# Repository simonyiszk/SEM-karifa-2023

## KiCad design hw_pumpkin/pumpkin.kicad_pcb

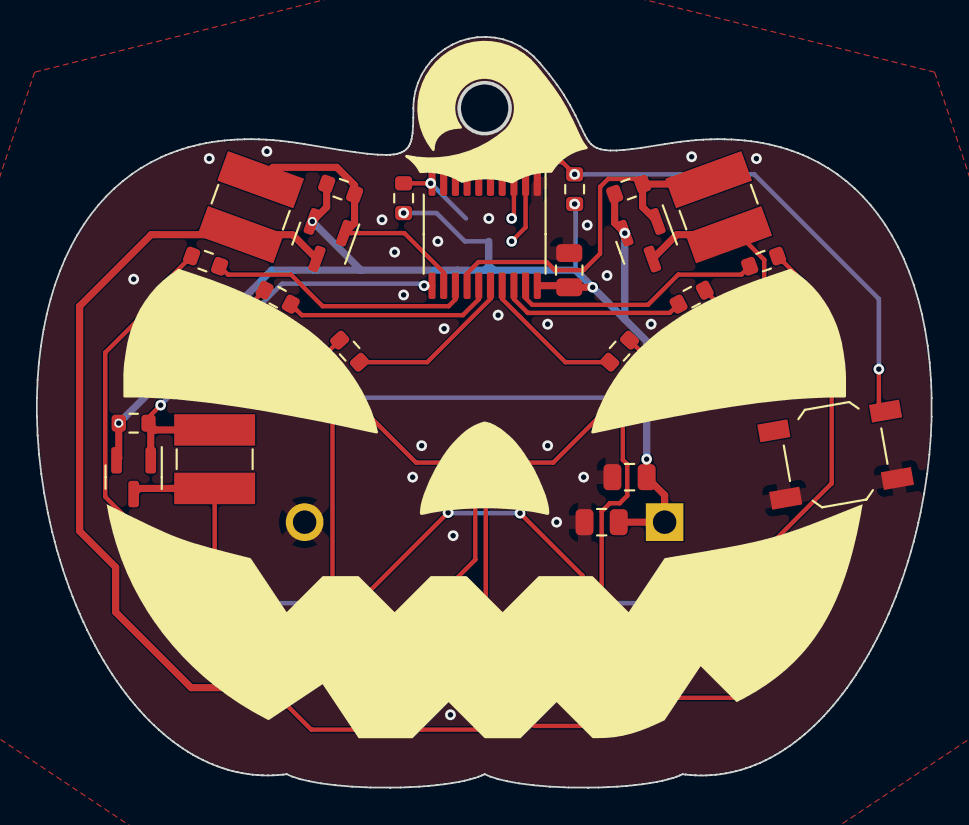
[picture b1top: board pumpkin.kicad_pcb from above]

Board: 2 copper layers, 49.7 x 41.7 mm, 44 parts (1 on the bottom side), 22 nets.

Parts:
BT1: CR2032; CR2032_Holder
C1, C2: 10uF; C_0805_2012Metric
C3: 100nF; C_0805_2012Metric
D1, D2, D3, D4, D5, D6, D7, D8, D9, D10, D11, D12, D13, D14, D15, D16, D17, D18: LED; LED_0805_2012Metric
L1, L2, L3: 1mH; L_Ferrocore_DLG-0403
Q1, Q2, Q3: AO3401A; SOT-23
R1, R6#2, R8, R9, R10: 100k; R_0603_1608Metric
R2, R3, R4, R5, R6, R7: 10; R_0603_1608Metric
SW1: SW_DPST_x2; SW_SPST_TL3342
T1, T1#2, T1#3: Tab
U1: PY32F002AF15P6TU; TSSOP-20_4.4x6.5mm_P0.65mm

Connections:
/L1: R2.2, U1.13 (PA2)
/L2: R3.2, U1.15 (PA4)
/L3: R4.2, U1.16 (PA7)
/L4: R5.2, U1.17 (PB0)
/L5: R6.2, U1.18 (PB2)
/L6: R7.2, U1.19 (PB1)
/MPX1: L1.2, Q1.1 (G), R1.2, U1.12 (PA1)
/MPX2: L2.2, Q2.1 (G), R8.2, U1.11 (PA0)
/MPX3: L3.2, Q3.1 (G), R10.2, U1.14 (PA3)
/nRST: R6#2.1, U1.10 (PF2-NRST)
GND: BT1.2 (-), C1.2, C2.2, C3.1, SW1.2 (B), U1.1 (VSS)
unnamed: D1.2 (A), D7.2 (A), D13.2 (A), R2.1
unnamed: D1.1 (K), D2.1 (K), D3.1 (K), D4.1 (K), D5.1 (K), D6.1 (K), L1.1, Q1.3 (D)
unnamed: D4.2 (A), D10.2 (A), D16.2 (A), R5.1
unnamed: D7.1 (K), D8.1 (K), D9.1 (K), D10.1 (K), D11.1 (K), D12.1 (K), L2.1, Q2.3 (D)
unnamed: D5.2 (A), D11.2 (A), D17.2 (A), R6.1
unnamed: D6.2 (A), D12.2 (A), D18.2 (A), R7.1
unnamed: D13.1 (K), D14.1 (K), D15.1 (K), D16.1 (K), D17.1 (K), D18.1 (K), L3.1, Q3.3 (D)
unnamed: D2.2 (A), D8.2 (A), D14.2 (A), R3.1
unnamed: D3.2 (A), D9.2 (A), D15.2 (A), R4.1
unnamed: R9.1, SW1.1 (A), U1.4 (PB3)
VCC: BT1.1 (+), C1.1, C2.1, C3.2, Q1.2 (S), Q2.2 (S), Q3.2 (S), R1.1, R6#2.2, R8.1, R9.2, R10.1, U1.20 (VCC)

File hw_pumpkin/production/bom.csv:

Designator,Footprint,Quantity,Value,LCSC Part #
BT1,CR2032_Holder,1,CR2032,
"C1, C2",0805,2,10uF,
C3,0805,1,100nF,
"D1, D10, D11, D12, D13, D14, D15, D16, D17, D18, D2, D3, D4, D5, D6, D7, D8, D9",0805,18,LED,
"L1, L2, L3",L_Ferrocore_DLG-0403,3,1mH,
"Q1, Q2, Q3",SOT-23,3,AO3401A,
"R1, R10, R6, R8, R9",0603,5,100k,
"R2, R3, R4, R5, R6_2, R7",0603,6,10,
SW1,SW_SPST_TL3342,1,SW_DPST_x2,
U1,TSSOP-20_4.4x6.5mm_P0.65mm,1,PY32F002AF15P6TU,

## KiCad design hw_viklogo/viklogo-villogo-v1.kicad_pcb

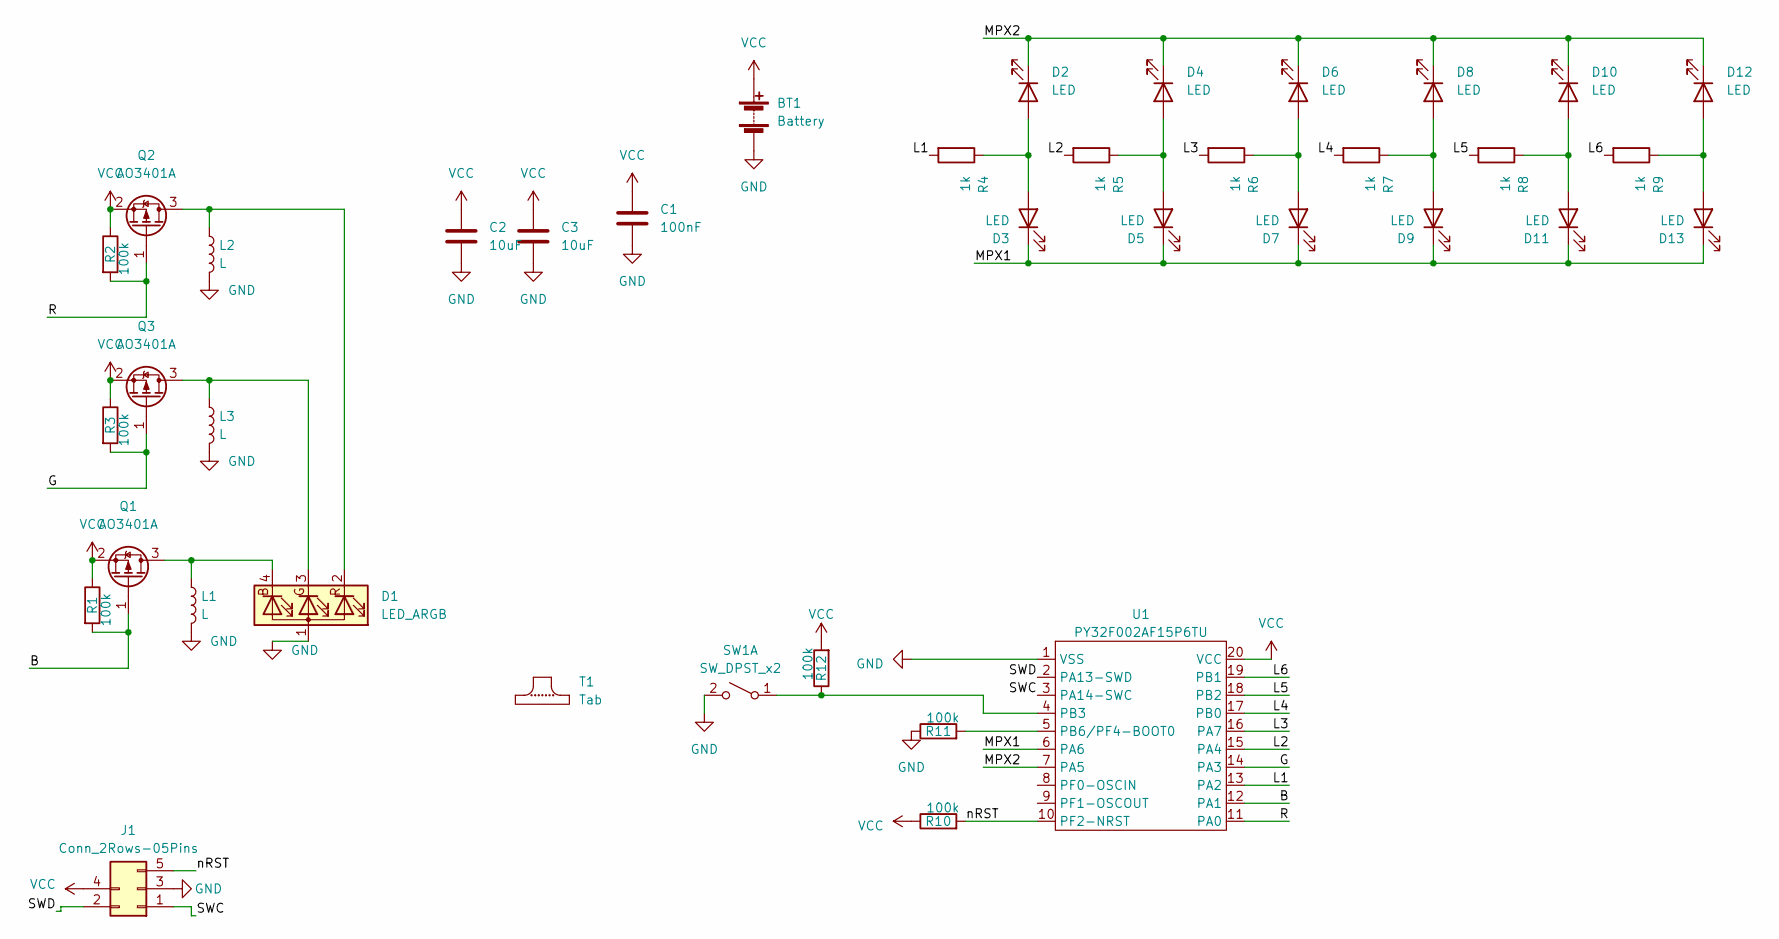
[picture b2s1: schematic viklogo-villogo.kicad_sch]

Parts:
BT1: Battery; CR2032_Holder
C1: 100nF; C_0805_2012Metric
C2, C3: 10uF; C_0805_2012Metric
D1: LED_ARGB; LED_RGB_Wuerth-PLCC4_3.2x2.8mm_150141M173100
D2, D3, D4, D5, D6, D7, D8, D9, D10, D11, D12, D13: LED; LED_0805_2012Metric
J1: Conn_2Rows-05Pins; ProgConnector_5pin
L1, L2, L3: L; L_1008_2520Metric
Q1, Q2, Q3: AO3401A; SOT-23
R1, R2, R3, R10, R11, R12: 100k; R_0603_1608Metric
R4, R5, R6, R7, R8, R9: 1k; R_0603_1608Metric
SW1: SW_DPST_x2; SW_SPST_TL3342
T1: Tab
U1: PY32F002AF15P6TU; TSSOP-20_4.4x6.5mm_P0.65mm

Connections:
/B: Q1.1 (G), R1.2, U1.12 (PA1)
/G: Q3.1 (G), R3.2, U1.14 (PA3)
/L1: R4.2, U1.13 (PA2)
/L2: R5.2, U1.15 (PA4)
/L3: R6.2, U1.16 (PA7)
/L4: R7.2, U1.17 (PB0)
/L5: R8.2, U1.18 (PB2)
/L6: R9.2, U1.19 (PB1)
/MPX1: D3.1 (K), D5.1 (K), D7.1 (K), D9.1 (K), D11.1 (K), D13.1 (K), U1.6 (PA6)
/MPX2: D2.1 (K), D4.1 (K), D6.1 (K), D8.1 (K), D10.1 (K), D12.1 (K), U1.7 (PA5)
/R: Q2.1 (G), R2.2, U1.11 (PA0)
/SWC: J1.1, U1.3 (PA14-SWC)
/SWD: J1.2, U1.2 (PA13-SWD)
/nRST: J1.5, R10.2, U1.10 (PF2-NRST)
GND: BT1.2 (-), C1.2, C2.2, C3.2, D1.1 (A), J1.3, L1.2, L2.2, L3.2, R11.1, SW1.2 (B), U1.1 (VSS)
unnamed: D1.4 (BK), L1.1, Q1.3 (D)
unnamed: D1.3 (GK), L3.1, Q3.3 (D)
unnamed: D1.2 (RK), L2.1, Q2.3 (D)
unnamed: D2.2 (A), D3.2 (A), R4.1
unnamed: D4.2 (A), D5.2 (A), R5.1
unnamed: D6.2 (A), D7.2 (A), R6.1
unnamed: D8.2 (A), D9.2 (A), R7.1
unnamed: D10.2 (A), D11.2 (A), R8.1
unnamed: D12.2 (A), D13.2 (A), R9.1
unnamed: R12.1, SW1.1 (A), U1.4 (PB3)
unnamed: R11.2, U1.5 (PB6/PF4-BOOT0)
VCC: BT1.1 (+), C1.1, C2.1, C3.1, J1.4, Q1.2 (S), Q2.2 (S), Q3.2 (S), R1.1, R2.1, R3.1, R10.1, R12.2, U1.20 (VCC)

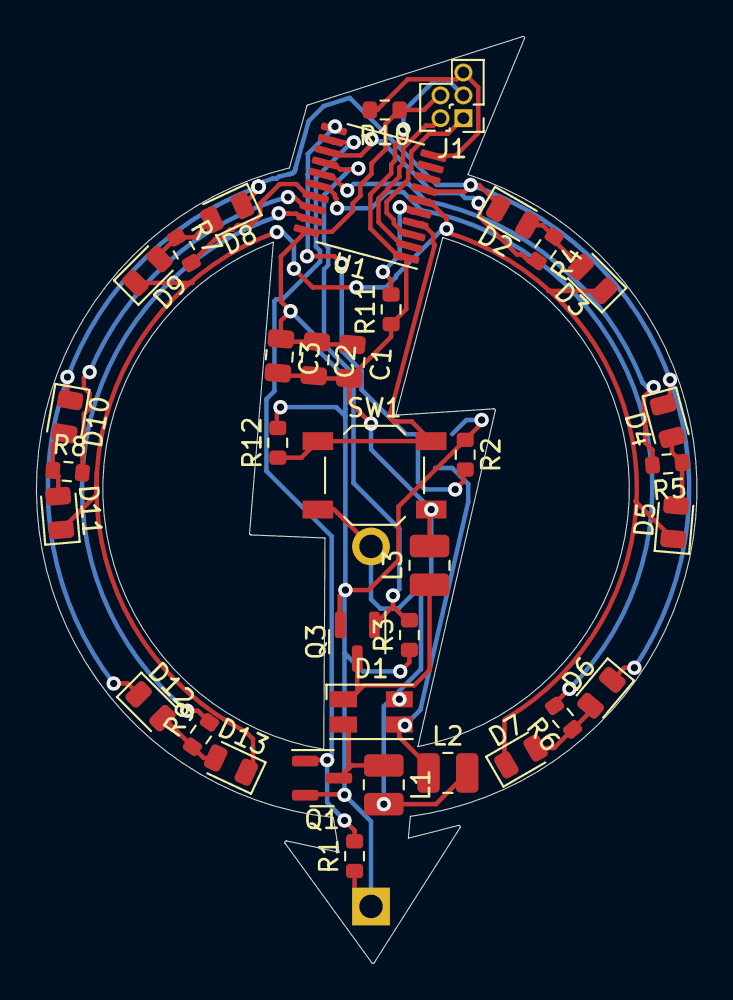
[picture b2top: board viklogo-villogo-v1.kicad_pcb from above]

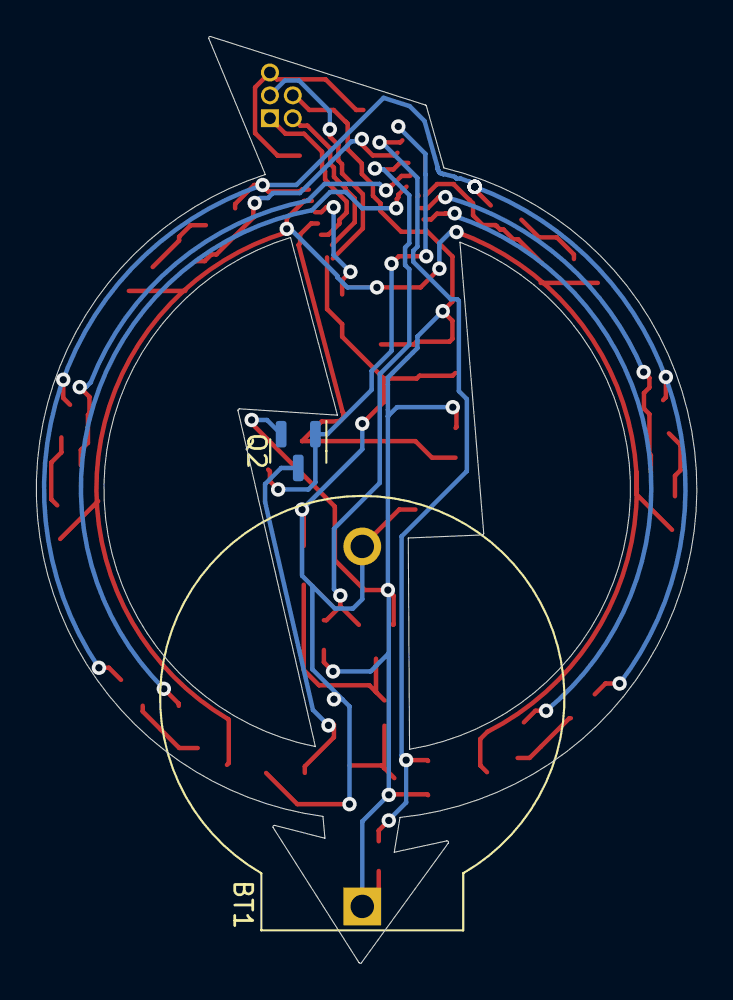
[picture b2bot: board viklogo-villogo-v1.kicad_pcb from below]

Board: 2 copper layers, 36.7 x 51.5 mm, 38 parts (2 on the bottom side), 27 nets.
